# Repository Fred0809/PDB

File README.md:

# PDB
The project uses XT60 conenctor for battery input and screw terminals for ESCs output. The board idea is to have fuse, current measurement, and buck converter to 5V. Curent measuremnt from INA amp is sent to FCU, mounted above, with JST-XH conenctor together with 5V, VBAT voltage measurement, and GND.

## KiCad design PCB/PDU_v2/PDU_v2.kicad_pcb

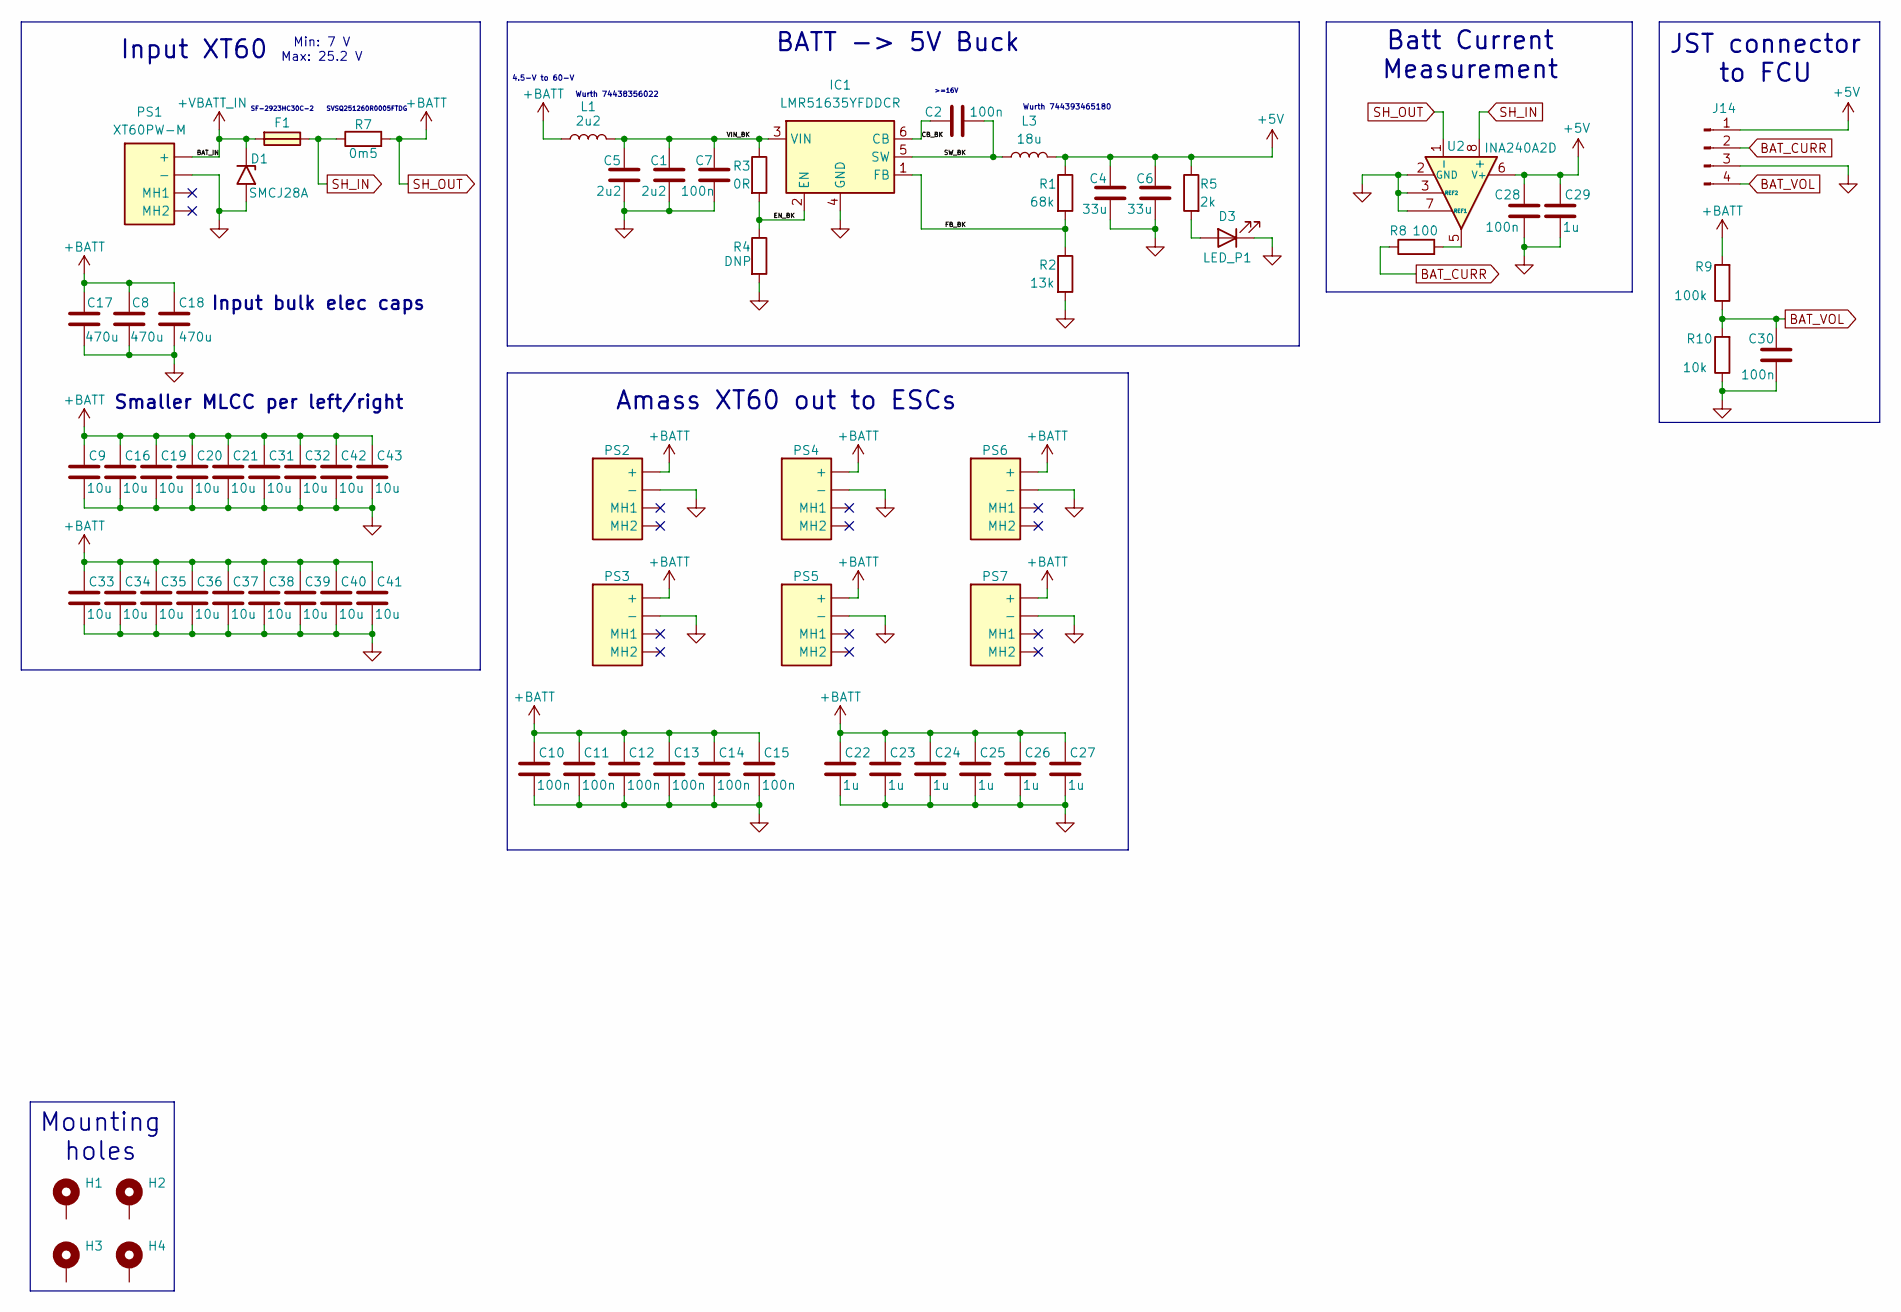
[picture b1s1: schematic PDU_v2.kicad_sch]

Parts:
C1, C5: 2u2; C_1210_3225Metric_Pad1.33x2.70mm_HandSolder
C2, C7, C30: 100n; C_0805_2012Metric_Pad1.18x1.45mm_HandSolder
C4, C6: 33u; C_1210_3225Metric_Pad1.33x2.70mm_HandSolder
C8, C17, C18: 470u; CP_Elec_8x10
C9, C16, C19, C20, C21, C31, C32, C33, C34, C35, C36, C37, C38, C39, C40, C41, C42, C43: 10u; C_1210_3225Metric_Pad1.33x2.70mm_HandSolder
C10, C11, C12, C13, C14, C15: 100n; C_1210_3225Metric_Pad1.33x2.70mm_HandSolder
C22, C23, C24, C25, C26, C27: 1u; C_1210_3225Metric_Pad1.33x2.70mm_HandSolder
C28: 100n; C_0603_1608Metric_Pad1.08x0.95mm_HandSolder
C29: 1u; C_0805_2012Metric_Pad1.18x1.45mm_HandSolder
D1: SMCJ28A; D_SMC
D3: LED_P1; LED_0805_2012Metric_Pad1.15x1.40mm_HandSolder
F1: SF-2923HC30C-2; SF2923HC30C2; Mouser Part Number 652-SF-2923HC30C-2
H1, H2, H3, H4: MountingHole_Pad; MountingHole_3.2mm_M3_ISO14580_Pad
IC1: LMR51635YFDDCR; SOT95P280X110-6N; Mouser Part Number 595-LMR51635YDDCR
J14: Conn_01x04_Pin; JST_XH_S4B-XH-A_1x04_P2.50mm_Horizontal
L1: 2u2; WE-MAPI_4020; Mouser Part Number 710-74438356022
L3: 18u; L_Coilcraft_XAL6060-XXX
PS1, PS2, PS3, PS4, PS5, PS6, PS7: XT60PW-M; XT60PWM; Manufacturer_Part_Number XT60PW-M
R1: 68k; R_0603_1608Metric_Pad0.98x0.95mm_HandSolder
R2: 13k; R_0603_1608Metric_Pad0.98x0.95mm_HandSolder
R3: 0R; R_0603_1608Metric_Pad0.98x0.95mm_HandSolder
R4: DNP; R_0603_1608Metric_Pad0.98x0.95mm_HandSolder
R5: 2k; R_0603_1608Metric_Pad0.98x0.95mm_HandSolder
R7: 0m5; R_2512_6332Metric_Pad1.40x3.35mm_HandSolder
R8: 100; R_0603_1608Metric_Pad0.98x0.95mm_HandSolder
R9: 100k; R_0603_1608Metric_Pad0.98x0.95mm_HandSolder
R10: 10k; R_0603_1608Metric_Pad0.98x0.95mm_HandSolder
U2: INA240A2D; SOIC-8_3.9x4.9mm_P1.27mm

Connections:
+5V: C4.1, C6.1, C28.2, C29.2, J14.1, L3.2, R1.1, R5.1, U2.6 (V+)
+VBATT_IN: D1.1 (A1), F1.1, PS1.1 (+); also elsewhere on the board
/CB_BK: C2.1, IC1.6 (CB)
/EN_BK: IC1.2 (EN), R3.2, R4.1
/FB_BK: IC1.1 (FB), R1.2, R2.1
/SW_BK: C2.2, IC1.5 (SW), L3.1
/VIN_BK: C1.1, C5.1, C7.1, IC1.3 (VIN), L1.2, R3.1
BAT_CURR: J14.2, R8.1
BAT_VOL: C30.2, J14.4, R9.1, R10.2
GND: C1.2, C4.2, C5.2, C6.2, C7.2, C8.2, C9.1, C10.1, C11.1, C12.1, C13.1, C14.1, C15.1, C16.1, C17.2, C18.2, C19.1, C20.1, C21.1, C22.1, C23.1, C24.1, C25.1, C26.1, C27.1, C28.1, C29.1, C30.1, C31.1, C32.1, C33.1, C34.1, C35.1, C36.1, C37.1, C38.1, C39.1, C40.1, C41.1, C42.1, C43.1, D1.2 (A2), D3.1 (K), IC1.4 (GND), J14.3, PS1.2 (-), PS2.2 (-), PS3.2 (-), PS4.2 (-), PS5.2 (-), PS6.2 (-), PS7.2 (-), R2.2, R4.2, R10.1, U2.2 (GND), U2.3 (REF2), U2.4 (GND), U2.7 (REF1); also elsewhere on the board
unnamed: D3.2 (A), R5.2
unnamed: R8.2, U2.5
SH_IN: F1.2, R7.1, U2.8 (+)
SH_OUT: C8.1, C9.2, C10.2, C11.2, C12.2, C13.2, C14.2, C15.2, C16.2, C17.1, C18.1, C19.2, C20.2, C21.2, C22.2, C23.2, C24.2, C25.2, C26.2, C27.2, C31.2, C32.2, C33.2, C34.2, C35.2, C36.2, C37.2, C38.2, C39.2, C40.2, C41.2, C42.2, C43.2, L1.1, PS2.1 (+), PS3.1 (+), PS4.1 (+), PS5.1 (+), PS6.1 (+), PS7.1 (+), R7.2, R9.2, U2.1 (-)

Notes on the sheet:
Mounting holes
4.5-V to 60-V
BATT -> 5V Buck
Input bulk elec caps
SF-2923HC30C-2
Input XT60
Min: 7 V Max: 25.2 V
>=16V
JST connector to FCU
Amass XT60 out to ESCs
Wurth 744393465180
Batt Current Measurement
SVSQ251260R0005FTDG
Wurth 74438356022
Smaller MLCC per left/right

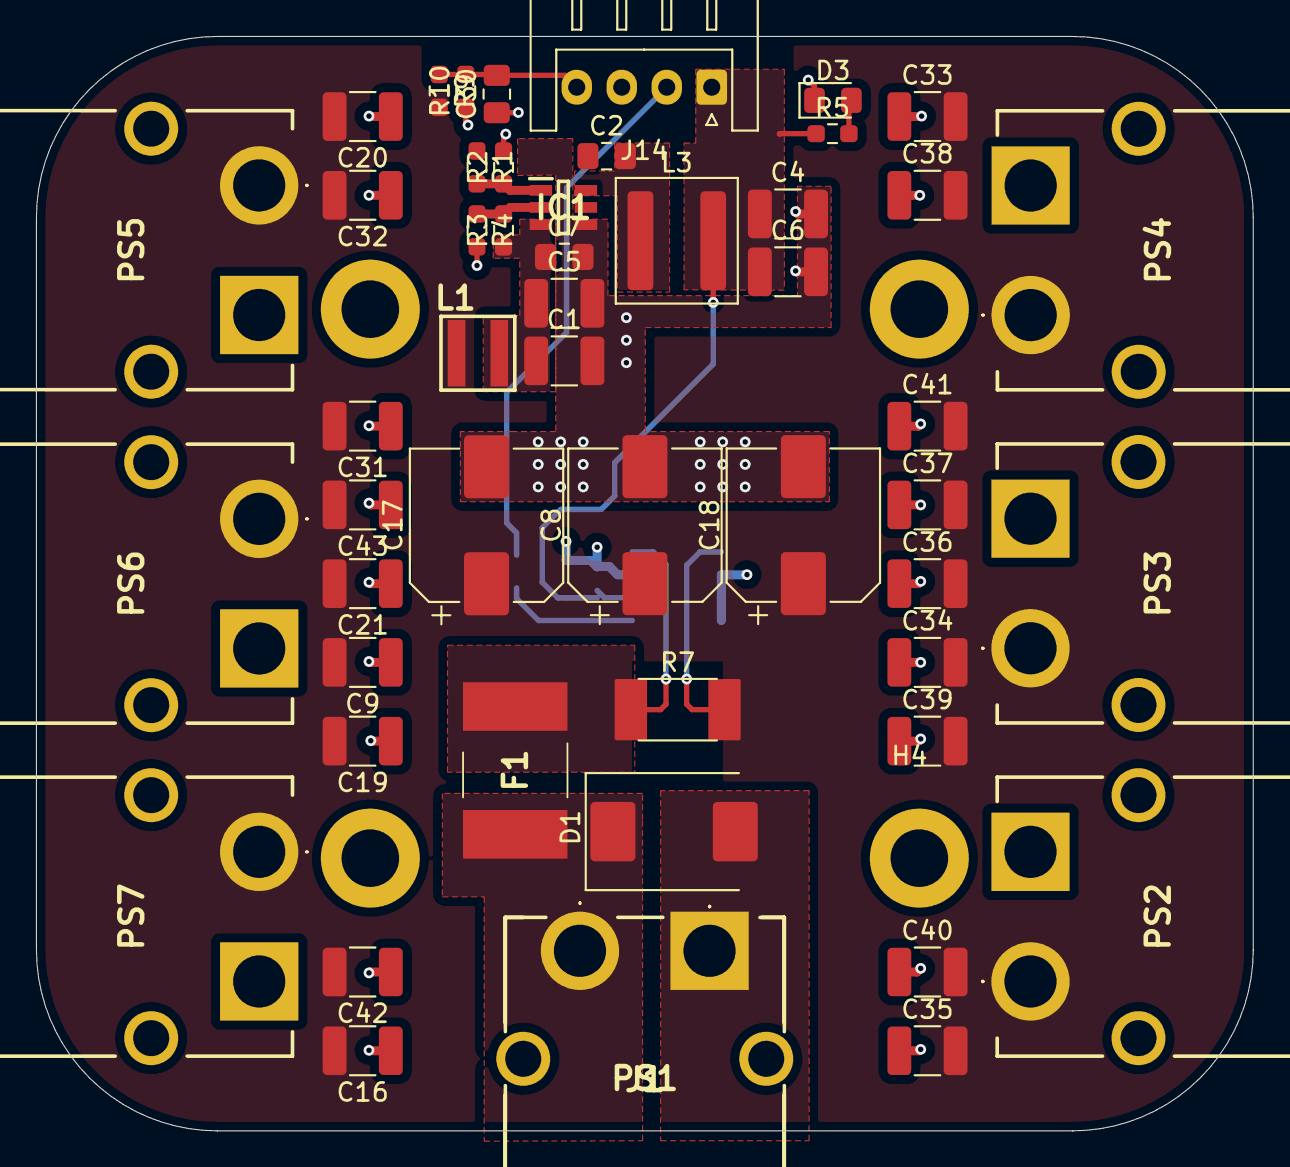
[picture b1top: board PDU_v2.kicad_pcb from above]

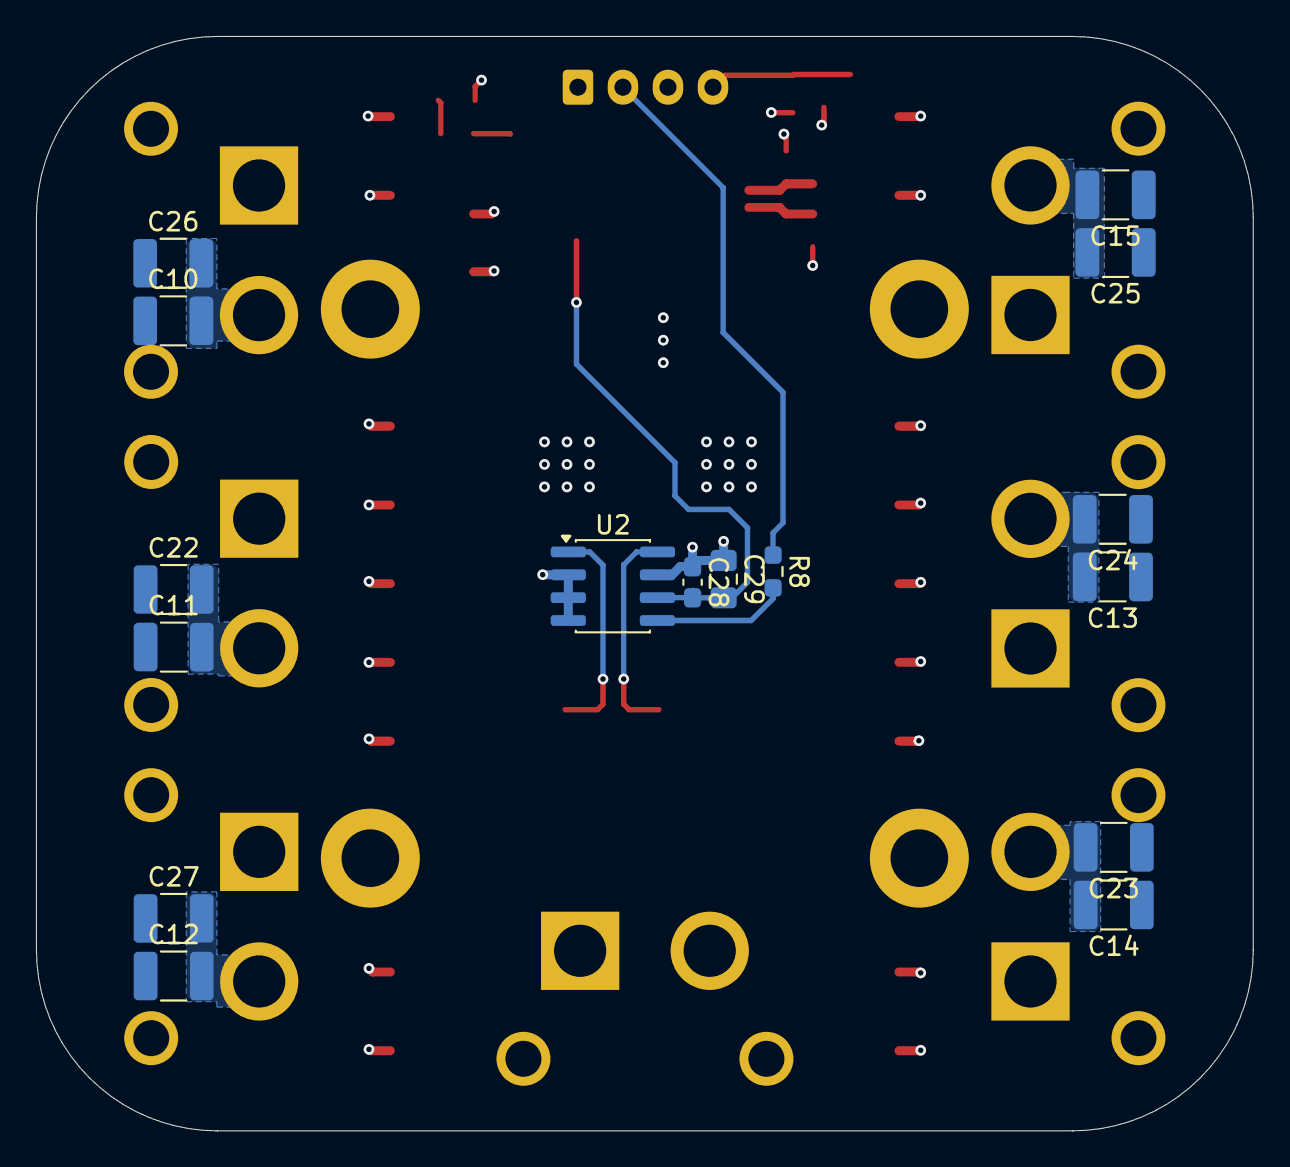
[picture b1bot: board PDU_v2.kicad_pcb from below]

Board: 4 copper layers, 67.6 x 60.8 mm, 71 parts (16 on the bottom side), 14 nets.

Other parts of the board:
J1: XT60PW-M; XT60PWM

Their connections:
+VBATT_IN: J1.1; also elsewhere on the board
GND: J1.2; also elsewhere on the board

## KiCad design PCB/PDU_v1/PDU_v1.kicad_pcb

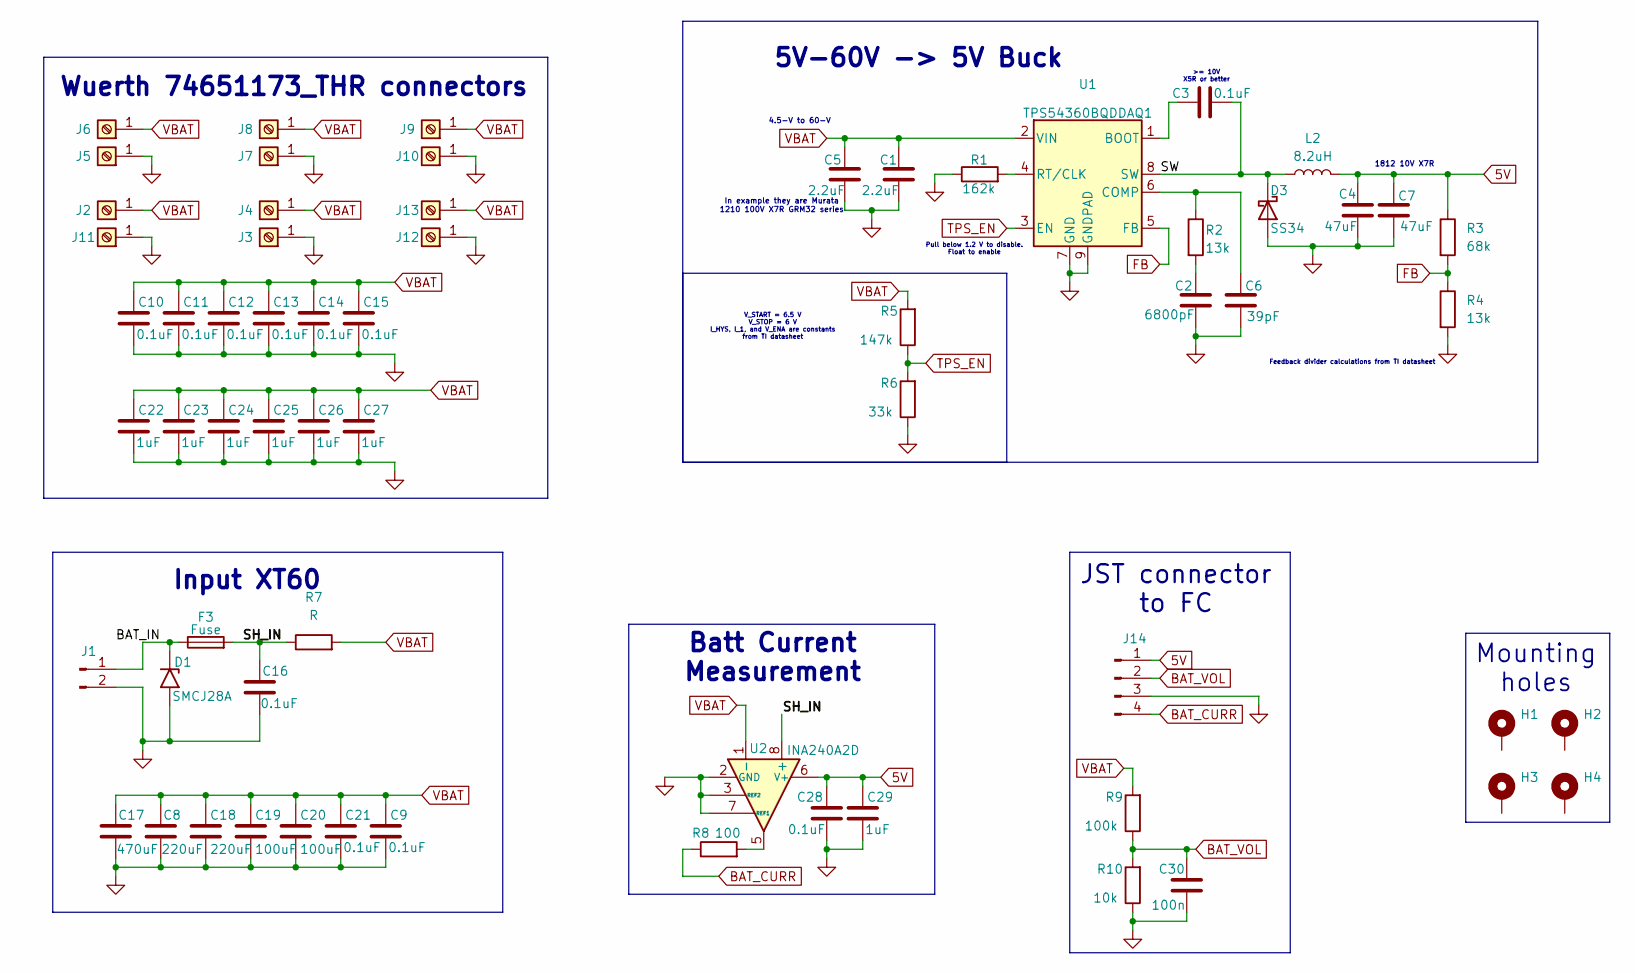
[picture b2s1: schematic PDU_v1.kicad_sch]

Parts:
C1, C5: 2.2uF; C_1210_3225Metric_Pad1.33x2.70mm_HandSolder
C2: 6800pF; C_0805_2012Metric_Pad1.18x1.45mm_HandSolder
C3, C9, C10, C11, C12, C13, C14, C15, C16, C21, C28: 0.1uF; C_0805_2012Metric_Pad1.18x1.45mm_HandSolder
C4, C7: 47uF; C_0805_2012Metric_Pad1.18x1.45mm_HandSolder
C6: 39pF; C_0805_2012Metric_Pad1.18x1.45mm_HandSolder
C8, C18: 220uF; C_1825_4564Metric_Pad1.57x6.80mm_HandSolder
C17: 470uF; C_1825_4564Metric_Pad1.57x6.80mm_HandSolder
C19, C20: 100uF; C_1825_4564Metric_Pad1.57x6.80mm_HandSolder
C22, C23, C24, C25, C26, C27, C29: 1uF; C_0805_2012Metric_Pad1.18x1.45mm_HandSolder
C30: 100n; C_0805_2012Metric_Pad1.18x1.45mm_HandSolder
D1: SMCJ28A; D_SMC
D3: SS34; D_SMA
F3: Fuse; Fuse_2920_7451Metric_Pad2.10x5.45mm_HandSolder
H1, H2, H3, H4: MountingHole_Pad; MountingHole_3.2mm_M3_ISO14580_Pad
J1: Conn_01x02_Pin; AMASS_XT60PW-M_1x02_P7.20mm_Horizontal
J2, J3, J4, J5, J6, J7, J8, J9, J10, J11, J12, J13: Screw_Terminal_01x01; Wuerth_REDCUBE-THR_WP-THRSH_74651173_THR
J14: Conn_01x04_Pin; JST_XH_S4B-XH-A_1x04_P2.50mm_Horizontal
L2: 8.2uH; L_Coilcraft_XAL6060-XXX
R1: 162k; R_0603_1608Metric_Pad0.98x0.95mm_HandSolder
R2, R4: 13k; R_0603_1608Metric_Pad0.98x0.95mm_HandSolder
R3: 68k; R_0603_1608Metric_Pad0.98x0.95mm_HandSolder
R5: 147k; R_0603_1608Metric_Pad0.98x0.95mm_HandSolder
R6: 33k; R_0603_1608Metric_Pad0.98x0.95mm_HandSolder
R7: R; R_Shunt_Vishay_WSR2_WSR3
R8: 100; R_0603_1608Metric_Pad0.98x0.95mm_HandSolder
R9: 100k; R_0603_1608Metric_Pad0.98x0.95mm_HandSolder
R10: 10k; R_0603_1608Metric_Pad0.98x0.95mm_HandSolder
U1: TPS54360BQDDAQ1; TI_SO-PowerPAD-8_ThermalVias
U2: INA240A2D; SOIC-8_3.9x4.9mm_P1.27mm

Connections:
5V: C4.1, C7.1, C28.2, C29.2, J14.1, L2.2, R3.1, U2.6 (V+)
/BAT_IN: D1.1 (A1), F3.1, J1.1
/SH_IN: C16.2, F3.2, R7.1, U2.8 (+)
/SW: C3.2, D3.1 (K), L2.1, U1.8 (SW)
BAT_CURR: J14.4, R8.1
BAT_VOL: C30.2, J14.2, R9.1, R10.2
FB: R3.2, R4.1, U1.5 (FB)
GND: C1.2, C2.2, C4.2, C5.2, C6.2, C7.2, C8.2, C9.1, C10.1, C11.1, C12.1, C13.1, C14.1, C15.1, C16.1, C17.2, C18.2, C19.2, C20.2, C21.1, C22.1, C23.1, C24.1, C25.1, C26.1, C27.1, C28.1, C29.1, C30.1, D1.2 (A2), D3.2 (A), J1.2, J3.1, J5.1, J7.1, J10.1, J11.1, J12.1, J14.3, R1.1, R4.2, R6.1, R10.1, U1.7 (GND), U1.9 (GNDPAD), U2.2 (GND), U2.3 (REF2), U2.4 (GND), U2.7 (REF1)
unnamed: C2.1, R2.2
unnamed: R8.2, U2.5
unnamed: C3.1, U1.1 (BOOT)
unnamed: C6.1, R2.1, U1.6 (COMP)
unnamed: R1.2, U1.4 (RT/CLK)
TPS_EN: R5.1, R6.2, U1.3 (EN)
VBAT: C1.1, C5.1, C8.1, C9.2, C10.2, C11.2, C12.2, C13.2, C14.2, C15.2, C17.1, C18.1, C19.1, C20.1, C21.2, C22.2, C23.2, C24.2, C25.2, C26.2, C27.2, J2.1, J4.1, J6.1, J8.1, J9.1, J13.1, R5.2, R7.2, R9.2, U1.2 (VIN), U2.1 (-)

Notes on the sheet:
V_START = 6.5 V V_STOP = 6 V I_HYS, I_1, and V_ENA are constants from TI datasheet
Mounting holes
4.5-V to 60-V
Pull below 1.2 V to disable. Float to enable
5V-60V -> 5V Buck
1812 10V X7R
Input XT60
Feedback divider calculations from TI datasheet
JST connector to FC
Wuerth 74651173_THR connectors
>= 10V X5R or better
In example they are Murata 1210 100V X7R GRM32 series
Batt Current Measurement

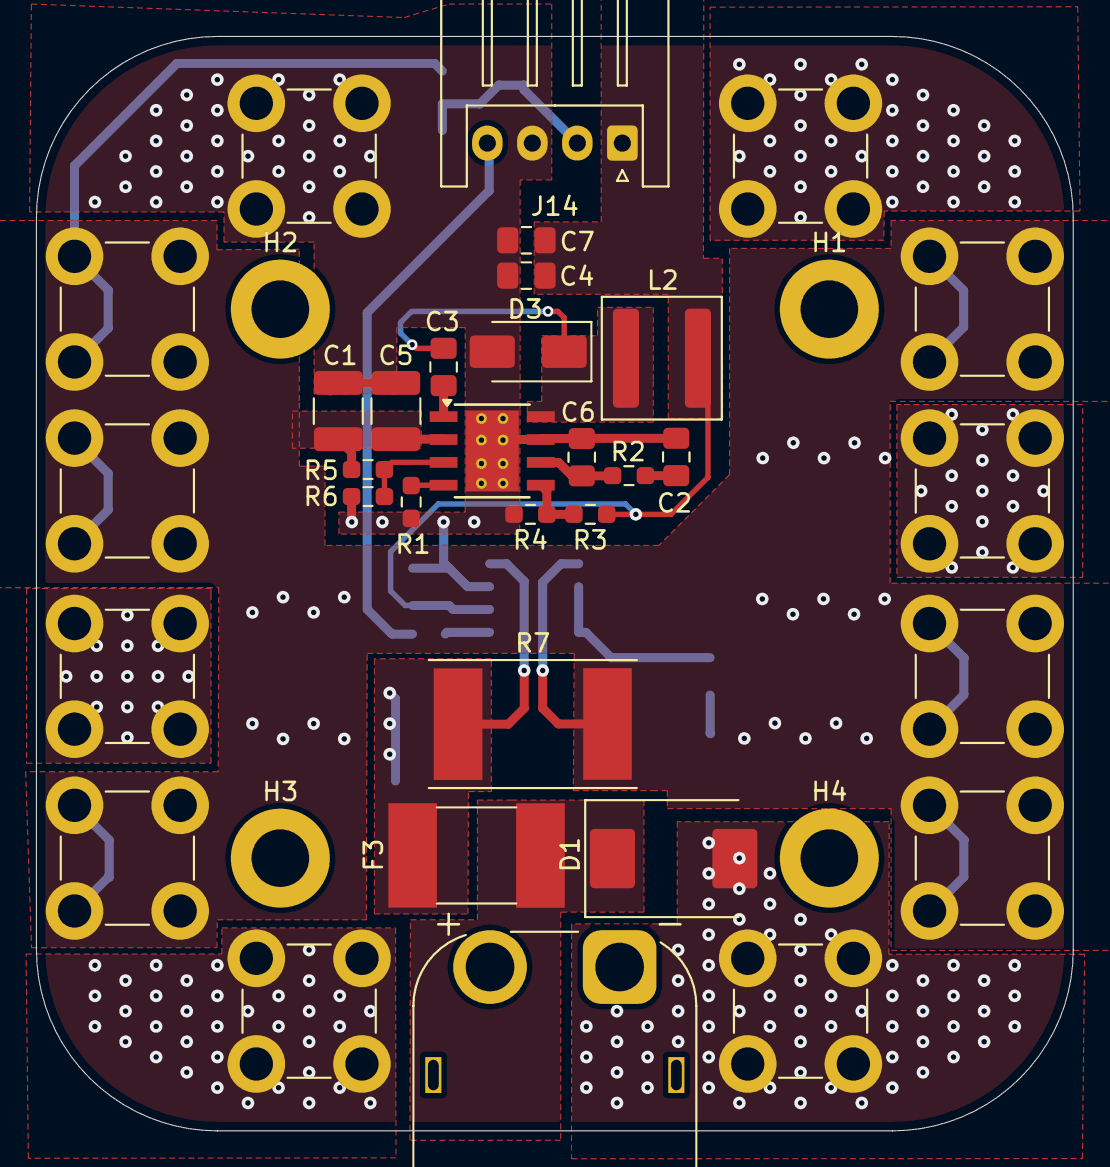
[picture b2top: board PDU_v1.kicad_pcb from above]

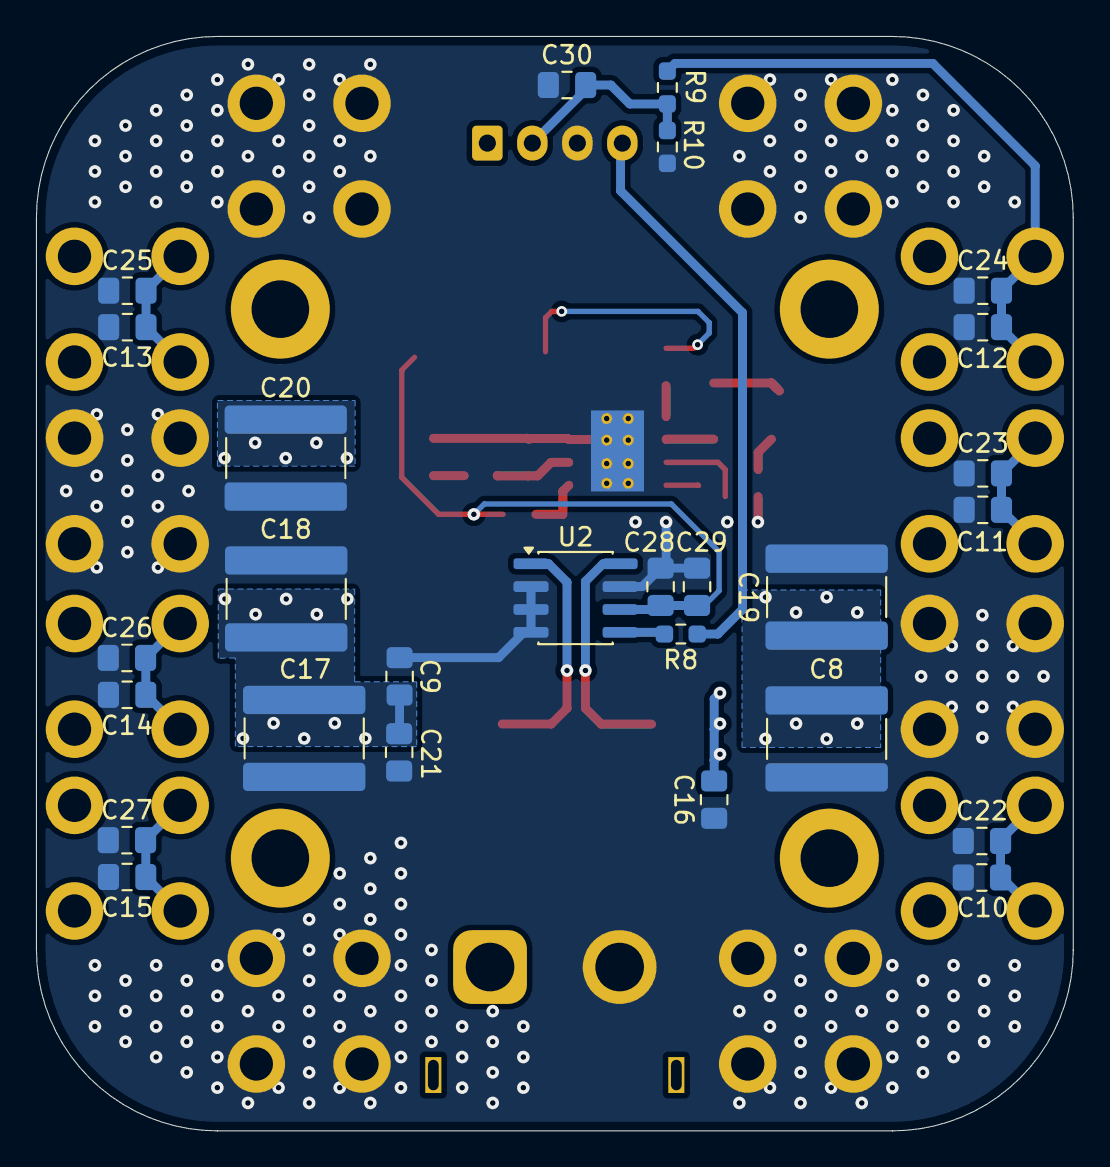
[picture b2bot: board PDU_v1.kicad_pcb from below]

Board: 2 copper layers, 57.6 x 60.8 mm, 64 parts (27 on the bottom side), 15 nets.

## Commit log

2026-01-30 Add PDU_v1 PCB design files and backups
    Initial commit of the PDU_v1 KiCad project, including schematic, PCB layout, project files, backup archives, and output images (PCB and schematic PDF).
2026-01-30 Enhance README with project details
    Added details about the XT60 connector, screw terminals, and current measurement.
2026-02-01 Changed description in README.md
    Changed the project description.
2026-02-01 changed wording in README about current measurement
2026-02-06 Update PCB nets, footprint positions and routes
    Rename and reassign nets for clarity (e.g. Net-(J14-Pin_4) -> BAT_VOL, adjust BAT_CURR and /BAT_IN/GND assignments), adjust component placement (C30 moved and value normalized from "0.1uF" to "100n")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
2026-02-17 Created next version
2026-02-17 Started working on v2
2026-02-18 Finished layout
2026-02-20 Udate
2026-02-20 Repaired library
2026-02-23 Layout update
2026-03-04 REadme update
2026-03-04 README.md
